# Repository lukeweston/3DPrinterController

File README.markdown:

3D printer / CNC machine controller:   

The final system will be broken across three boards, to allow for modularity, replacement of the modules individually, upgradability, and to allow enough space for proper
design of the power electronics.   

a) Microcontroller, UI, storage, display, connectivity etc.   
b) Power distribution, switching, heater control etc.   
c) Stepper motor drivers.   

Example image of 5-channel stepper motor controller board:

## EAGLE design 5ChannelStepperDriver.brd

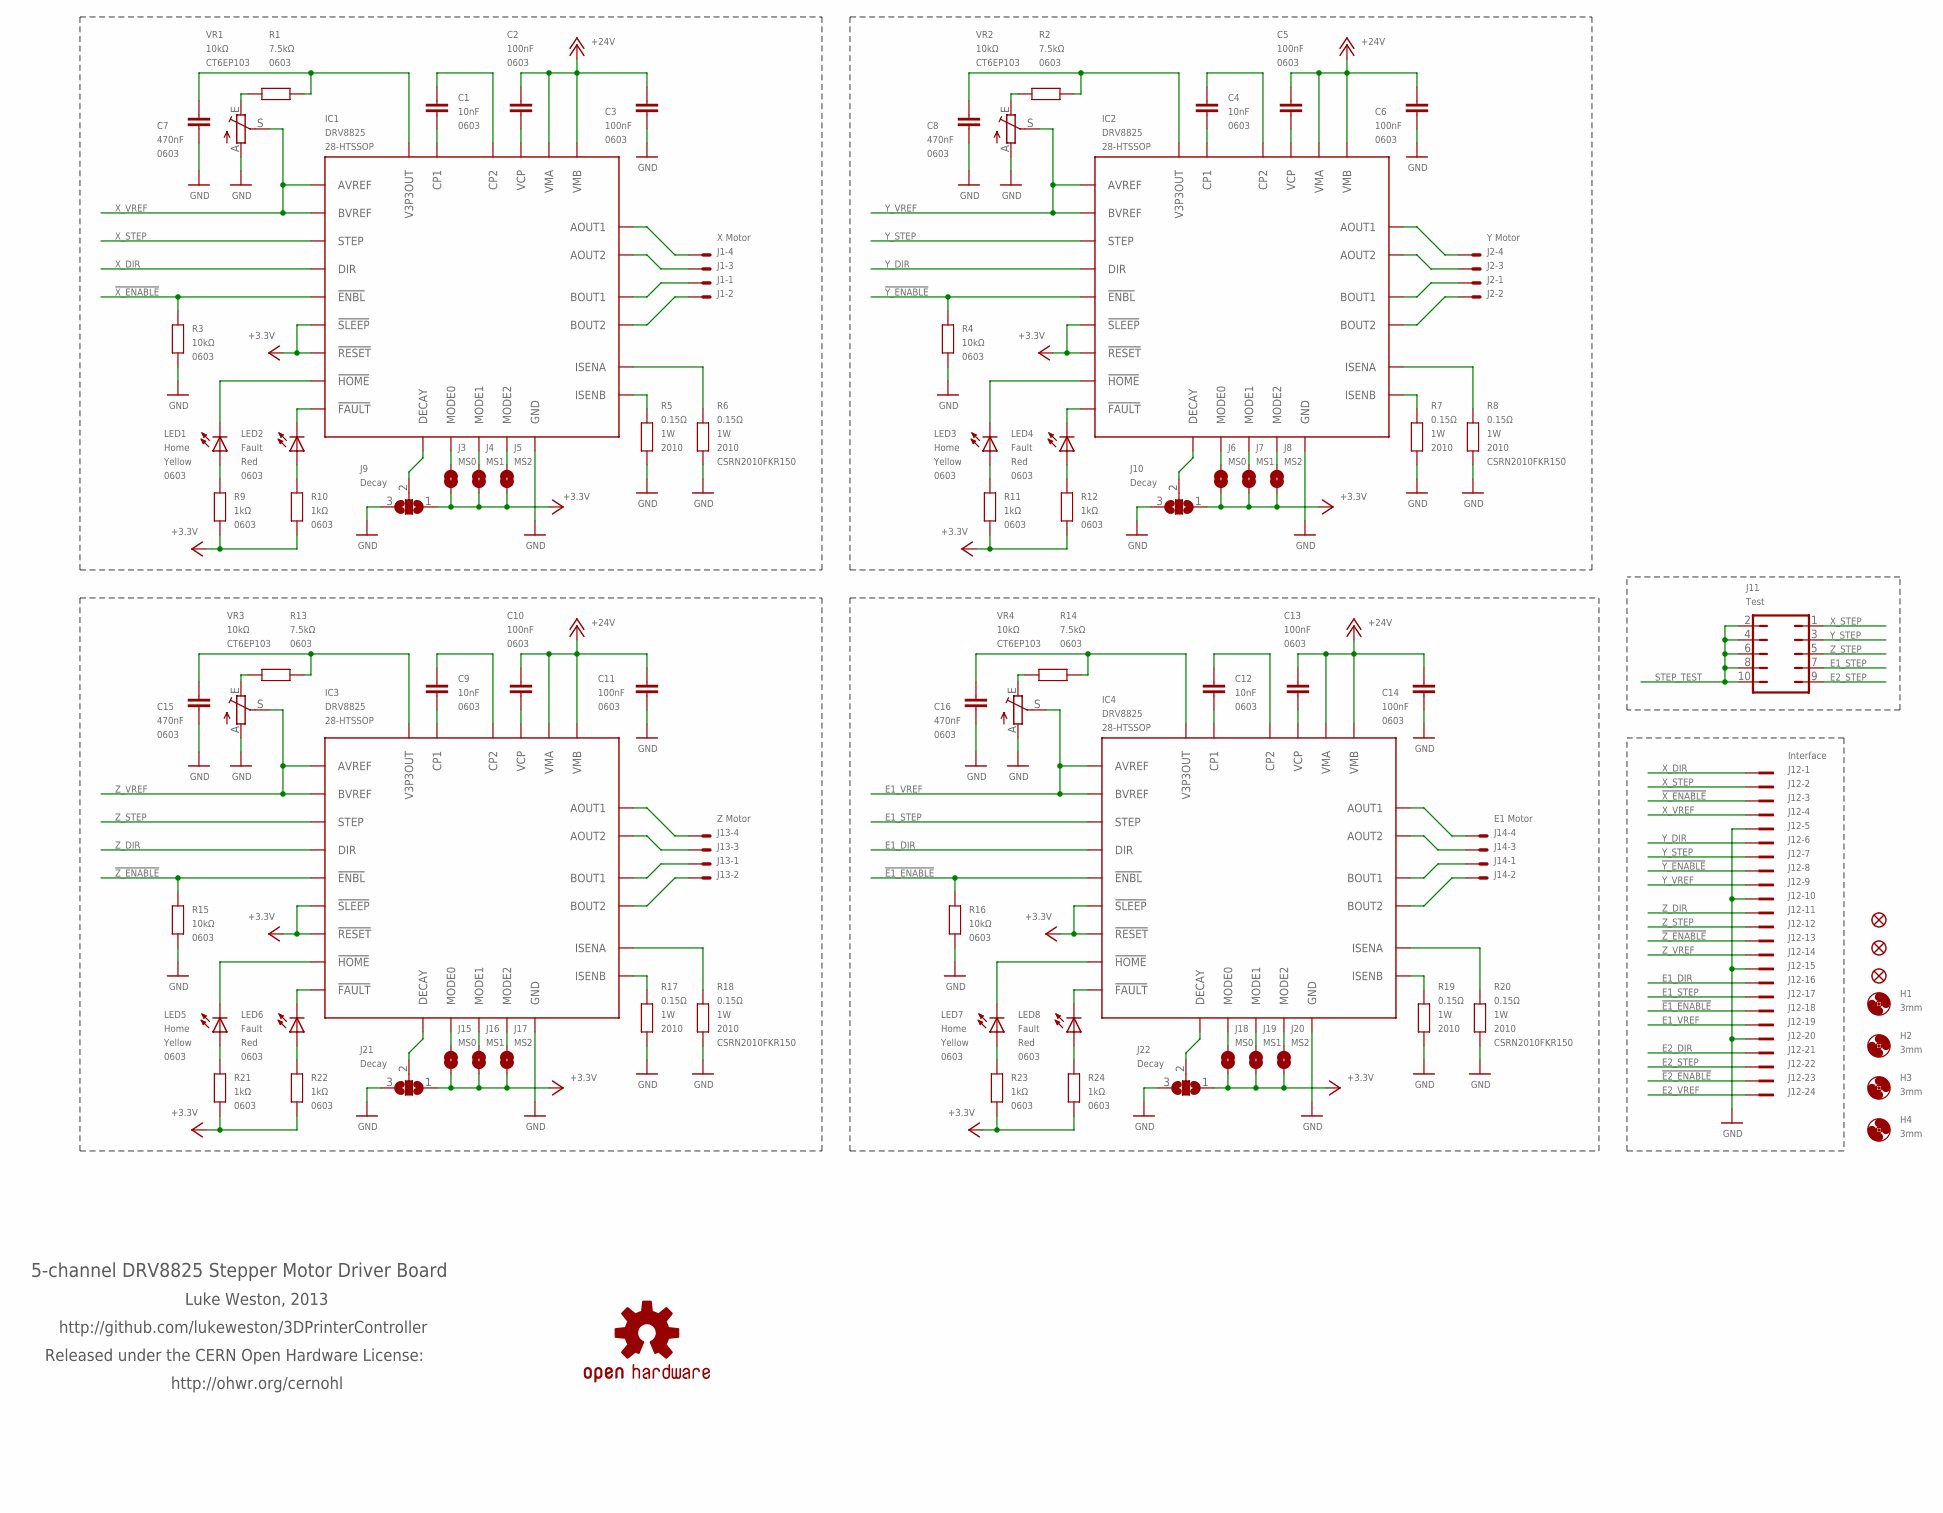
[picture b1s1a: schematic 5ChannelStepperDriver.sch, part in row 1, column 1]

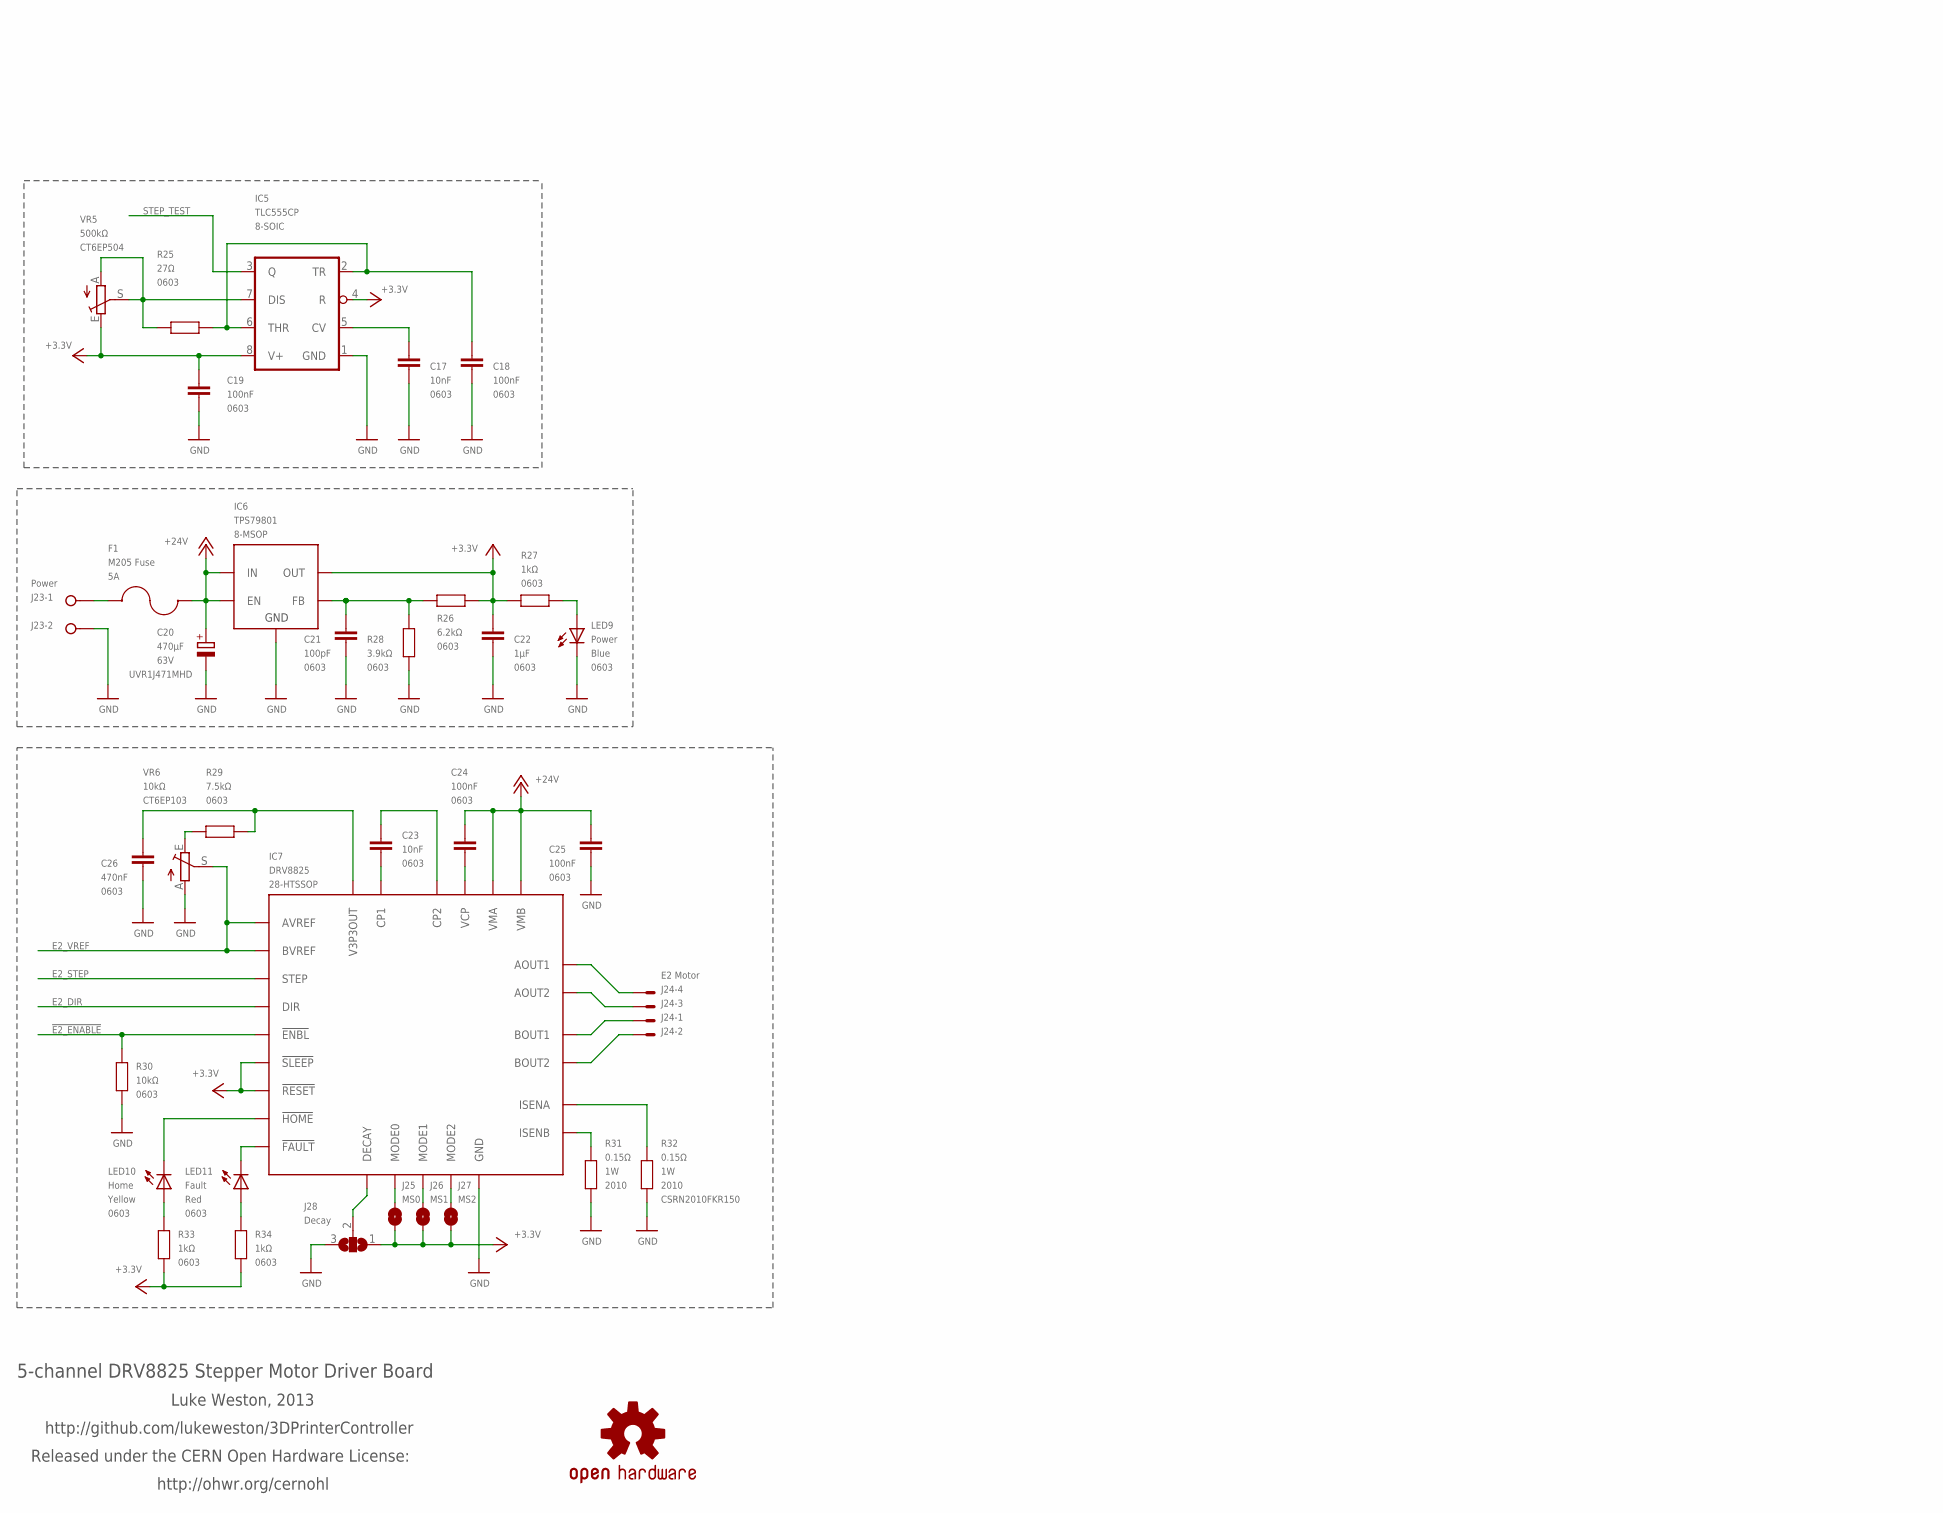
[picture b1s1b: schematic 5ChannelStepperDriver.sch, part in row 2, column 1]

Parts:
C1, C4, C9, C12, C17, C23: 10nF; 0603
C2, C3, C5, C6, C10, C11, C13, C14, C18, C19, C24, C25: 100nF; 0603
C7, C8, C15, C16, C26: 470nF; 0603
C20: 470µF; E5-13; VOLTAGE 63V
C21: 100pF; 0603
C22: 1µF; 0603
F1: M205 Fuse; FUSECLIP-FC211
H1, H2, H3, H4: 3mm; 3,0
IC1, IC2, IC3, IC4, IC7: DRV8825; R-PDSO-G28
IC5: TLC555CP; SO08
IC6: TPS79801; R-PDSO-G8
J1: X Motor; 7395-04
J2: Y Motor; 7395-04
J3, J6, J15, J18, J25: MS0; SJ
J4, J7, J16, J19, J26: MS1; SJ
J5, J8, J17, J20, J27: MS2; SJ
J9, J10, J21, J22, J28: Decay; SJ_2
J11: Test; JP5Q
J12: Interface; PAK100/2500-24
J13: Z Motor; 7395-04
J14: E1 Motor; 7395-04
J23: Power; W237-132
J24: E2 Motor; 7395-04
JP1, JP2, JP3: FIDUCIAL1X2; FIDUCIAL-1X2
LED1, LED3, LED5, LED7, LED10: Home; LED-0603
LED2, LED4, LED6, LED8, LED11: Fault; LED-0603
LED9: Power; LED-0603
R1, R2, R13, R14, R29: 7.5kΩ; 0603
R3, R4, R15, R16, R30: 10kΩ; 0603
R5, R6, R7, R8, R17, R18, R19, R20, R31, R32: 0.15Ω; R2010
R9, R10, R11, R12, R21, R22, R23, R24, R27, R33, R34: 1kΩ; 0603
R25: 27Ω; 0603
R26: 6.2kΩ; 0603
R28: 3.9kΩ; 0603
SY1, SY2: OSHW-LOGOS; OSHW-LOGO-S
VR1, VR2, VR3, VR4, VR6: 10kΩ; CT6
VR5: 500kΩ; CT6

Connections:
!E1_ENABLE: IC4.21 (!ENBL), J12.18, R16.1
!E2_ENABLE: IC7.21 (!ENBL), J12.23, R30.1
!X_ENABLE: IC1.21 (!ENBL), J12.3, R3.1
!Y_ENABLE: IC2.21 (!ENBL), J12.8, R4.1
!Z_ENABLE: IC3.21 (!ENBL), J12.13, R15.1
+3V3: C19.1, C22.1, IC1.16 (!RESET), IC1.17 (!SLEEP), IC2.16 (!RESET), IC2.17 (!SLEEP), IC3.16 (!RESET), IC3.17 (!SLEEP), IC4.16 (!RESET), IC4.17 (!SLEEP), IC5.4 (R), IC5.8 (V+), IC6.1 (OUT), IC7.16 (!RESET), IC7.17 (!SLEEP), J3.1, J4.1, J5.1, J6.1, J7.1, J8.1, J9.1, J10.1, J15.1, J16.1, J17.1, J18.1, J19.1, J20.1, J21.1, J22.1, J25.1, J26.1, J27.1, J28.1, R9.2, R10.2, R11.2, R12.2, R21.2, R22.2, R23.2, R24.2, R26.2, R27.2, R33.2, R34.2, VR5.E
+24V: C2.1, C3.1, C5.1, C6.1, C10.1, C11.1, C13.1, C14.1, C20.+, C24.1, C25.1, F1.3 (2), F1.4 (2), IC1.4 (VMA), IC1.11 (VMB), IC2.4 (VMA), IC2.11 (VMB), IC3.4 (VMA), IC3.11 (VMB), IC4.4 (VMA), IC4.11 (VMB), IC6.5 (EN), IC6.8 (IN), IC7.4 (VMA), IC7.11 (VMB)
E1_DIR: IC4.20 (DIR), J12.16
E1_STEP: IC4.22 (STEP), J11.7, J12.17
E1_VREF: IC4.12 (AVREF), IC4.13 (BVREF), J12.19, VR4.S
E2_DIR: IC7.20 (DIR), J12.21
E2_STEP: IC7.22 (STEP), J11.9, J12.22
E2_VREF: IC7.12 (AVREF), IC7.13 (BVREF), J12.24, VR6.S
GND: C3.2, C6.2, C7.2, C8.2, C11.2, C14.2, C15.2, C16.2, C17.2, C18.2, C19.2, C20.-, C21.2, C22.2, C25.2, C26.2, IC1.14 (GND), IC1.28 (GND), IC1.PAD (GND), IC2.14 (GND), IC2.28 (GND), IC2.PAD (GND), IC3.14 (GND), IC3.28 (GND), IC3.PAD (GND), IC4.14 (GND), IC4.28 (GND), IC4.PAD (GND), IC5.1 (GND), IC6.4 (GND), IC6.PAD (GND), IC7.14 (GND), IC7.28 (GND), IC7.PAD (GND), J9.3, J10.3, J12.5, J12.10, J12.15, J12.20, J21.3, J22.3, J23.2, J28.3, LED9.C, R3.2, R4.2, R5.2, R6.2, R7.2, R8.2, R15.2, R16.2, R17.2, R18.2, R19.2, R20.2, R28.2, R30.2, R31.2, R32.2, VR1.A, VR2.A, VR3.A, VR4.A, VR6.A
unnamed: IC1.5 (AOUT1), J1.4
unnamed: IC4.10 (BOUT1), J14.1
unnamed: IC3.10 (BOUT1), J13.1
unnamed: IC7.10 (BOUT1), J24.1
unnamed: IC7.7 (AOUT2), J24.3
unnamed: C7.1, IC1.15 (V3P3OUT), R1.1
unnamed: F1.1, F1.2 (1), J23.1
unnamed: R14.2, VR4.E
unnamed: C8.1, IC2.15 (V3P3OUT), R2.1
unnamed: C16.1, IC4.15 (V3P3OUT), R14.1
unnamed: C26.1, IC7.15 (V3P3OUT), R29.1
unnamed: R2.2, VR2.E
unnamed: R29.2, VR6.E
unnamed: R1.2, VR1.E
unnamed: C18.1, IC5.2 (TR), IC5.6 (THR), R25.1
unnamed: C15.1, IC3.15 (V3P3OUT), R13.1
unnamed: C21.1, IC6.2 (FB), R26.1, R28.1
unnamed: R13.2, VR3.E
unnamed: C17.1, IC5.5 (CV)
unnamed: LED9.A, R27.1
unnamed: IC5.7 (DIS), R25.2, VR5.A, VR5.S
unnamed: IC1.7 (AOUT2), J1.3
unnamed: IC1.10 (BOUT1), J1.1
unnamed: IC1.8 (BOUT2), J1.2
unnamed: C1.2, IC1.1 (CP1)
unnamed: C1.1, IC1.2 (CP2)
unnamed: IC1.19 (DECAY), J9.2
unnamed: C2.2, IC1.3 (VCP)
unnamed: IC1.6 (ISENA), R6.1
unnamed: IC3.5 (AOUT1), J13.4
unnamed: IC1.9 (ISENB), R5.1
unnamed: IC3.7 (AOUT2), J13.3
unnamed: IC3.8 (BOUT2), J13.2
unnamed: IC1.18 (!FAULT), LED2.C
unnamed: IC1.27 (!HOME), LED1.C
unnamed: LED1.A, R9.1
unnamed: LED2.A, R10.1
unnamed: IC1.25 (MODE1), J4.2
unnamed: IC1.26 (MODE2), J5.2
unnamed: IC1.24 (MODE0), J3.2
unnamed: C10.2, IC3.3 (VCP)
unnamed: IC3.6 (ISENA), R18.1
unnamed: IC3.9 (ISENB), R17.1
unnamed: IC3.18 (!FAULT), LED6.C
unnamed: IC3.27 (!HOME), LED5.C
unnamed: LED5.A, R21.1
unnamed: LED6.A, R22.1
unnamed: C9.2, IC3.1 (CP1)
unnamed: C9.1, IC3.2 (CP2)
unnamed: IC3.19 (DECAY), J21.2
unnamed: IC3.24 (MODE0), J15.2
unnamed: IC3.25 (MODE1), J16.2
unnamed: IC3.26 (MODE2), J17.2
unnamed: IC2.5 (AOUT1), J2.4
unnamed: IC2.7 (AOUT2), J2.3
unnamed: IC2.10 (BOUT1), J2.1
unnamed: IC2.8 (BOUT2), J2.2
unnamed: C5.2, IC2.3 (VCP)
unnamed: IC2.6 (ISENA), R8.1
unnamed: IC2.9 (ISENB), R7.1
unnamed: IC2.18 (!FAULT), LED4.C
unnamed: IC2.27 (!HOME), LED3.C
unnamed: LED3.A, R11.1
unnamed: LED4.A, R12.1
unnamed: C4.2, IC2.1 (CP1)
unnamed: C4.1, IC2.2 (CP2)
unnamed: IC2.19 (DECAY), J10.2
unnamed: IC2.24 (MODE0), J6.2
unnamed: IC2.25 (MODE1), J7.2
unnamed: IC2.26 (MODE2), J8.2
unnamed: IC4.5 (AOUT1), J14.4
unnamed: IC4.7 (AOUT2), J14.3
unnamed: IC4.8 (BOUT2), J14.2
unnamed: C13.2, IC4.3 (VCP)
unnamed: IC4.6 (ISENA), R20.1
unnamed: IC4.9 (ISENB), R19.1
unnamed: IC4.18 (!FAULT), LED8.C
unnamed: IC4.27 (!HOME), LED7.C
unnamed: LED7.A, R23.1
unnamed: LED8.A, R24.1
unnamed: C12.2, IC4.1 (CP1)
unnamed: C12.1, IC4.2 (CP2)
unnamed: IC4.19 (DECAY), J22.2
unnamed: IC4.24 (MODE0), J18.2
unnamed: IC4.25 (MODE1), J19.2
unnamed: IC4.26 (MODE2), J20.2
unnamed: IC7.5 (AOUT1), J24.4
unnamed: IC7.8 (BOUT2), J24.2
unnamed: C24.2, IC7.3 (VCP)
unnamed: IC7.6 (ISENA), R32.1
unnamed: IC7.9 (ISENB), R31.1
unnamed: IC7.18 (!FAULT), LED11.C
unnamed: IC7.27 (!HOME), LED10.C
unnamed: LED10.A, R33.1
unnamed: LED11.A, R34.1
unnamed: C23.2, IC7.1 (CP1)
unnamed: C23.1, IC7.2 (CP2)
unnamed: IC7.19 (DECAY), J28.2
unnamed: IC7.24 (MODE0), J25.2
unnamed: IC7.25 (MODE1), J26.2
unnamed: IC7.26 (MODE2), J27.2
STEP_TEST: IC5.3 (Q), J11.2, J11.4, J11.6, J11.8, J11.10
X_DIR: IC1.20 (DIR), J12.1
X_STEP: IC1.22 (STEP), J11.1, J12.2
X_VREF: IC1.12 (AVREF), IC1.13 (BVREF), J12.4, VR1.S
Y_DIR: IC2.20 (DIR), J12.6
Y_STEP: IC2.22 (STEP), J11.3, J12.7
Y_VREF: IC2.12 (AVREF), IC2.13 (BVREF), J12.9, VR2.S
Z_DIR: IC3.20 (DIR), J12.11
Z_STEP: IC3.22 (STEP), J11.5, J12.12
Z_VREF: IC3.12 (AVREF), IC3.13 (BVREF), J12.14, VR3.S

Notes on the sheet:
5-channel DRV8825 Stepper Motor Driver Board
Luke Weston, 2013
http://github.com/lukeweston/3DPrinterController
Released under the CERN Open Hardware License:
http://ohwr.org/cernohl

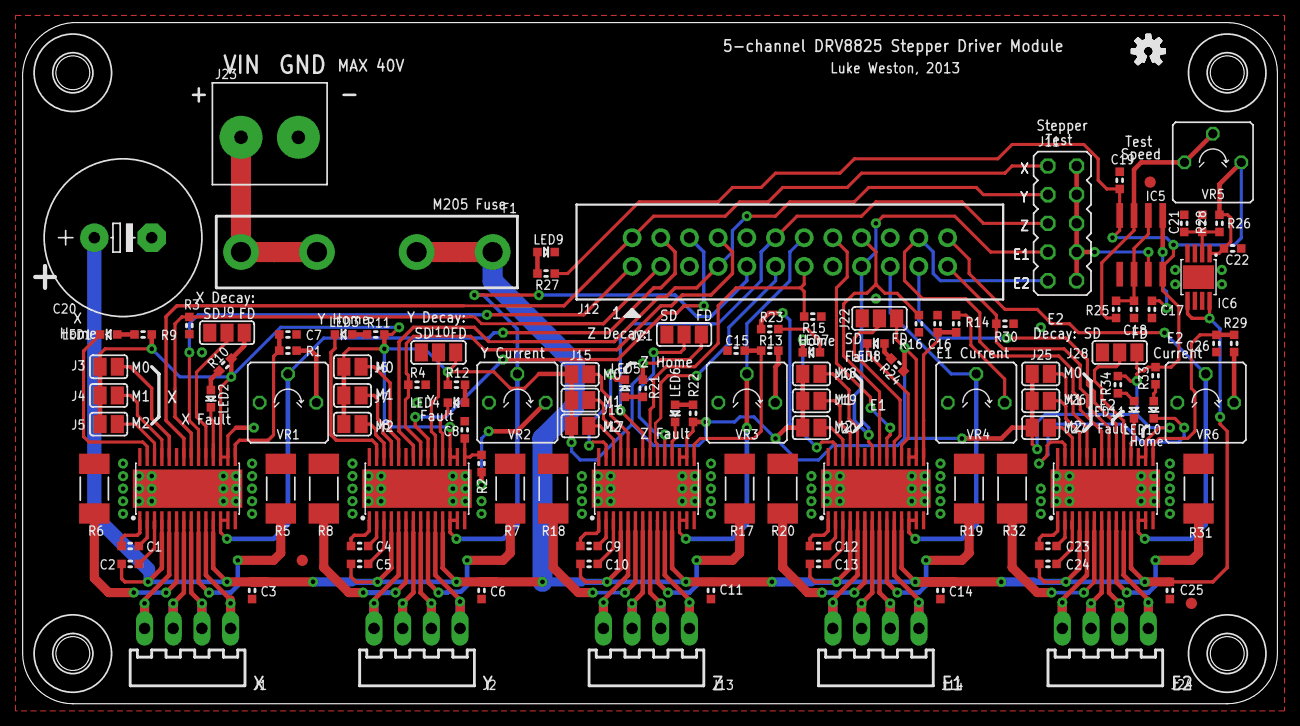
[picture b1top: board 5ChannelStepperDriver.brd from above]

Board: 2 copper layers, 111.1 x 60.3 mm, 122 parts (0 on the bottom side), 125 nets.

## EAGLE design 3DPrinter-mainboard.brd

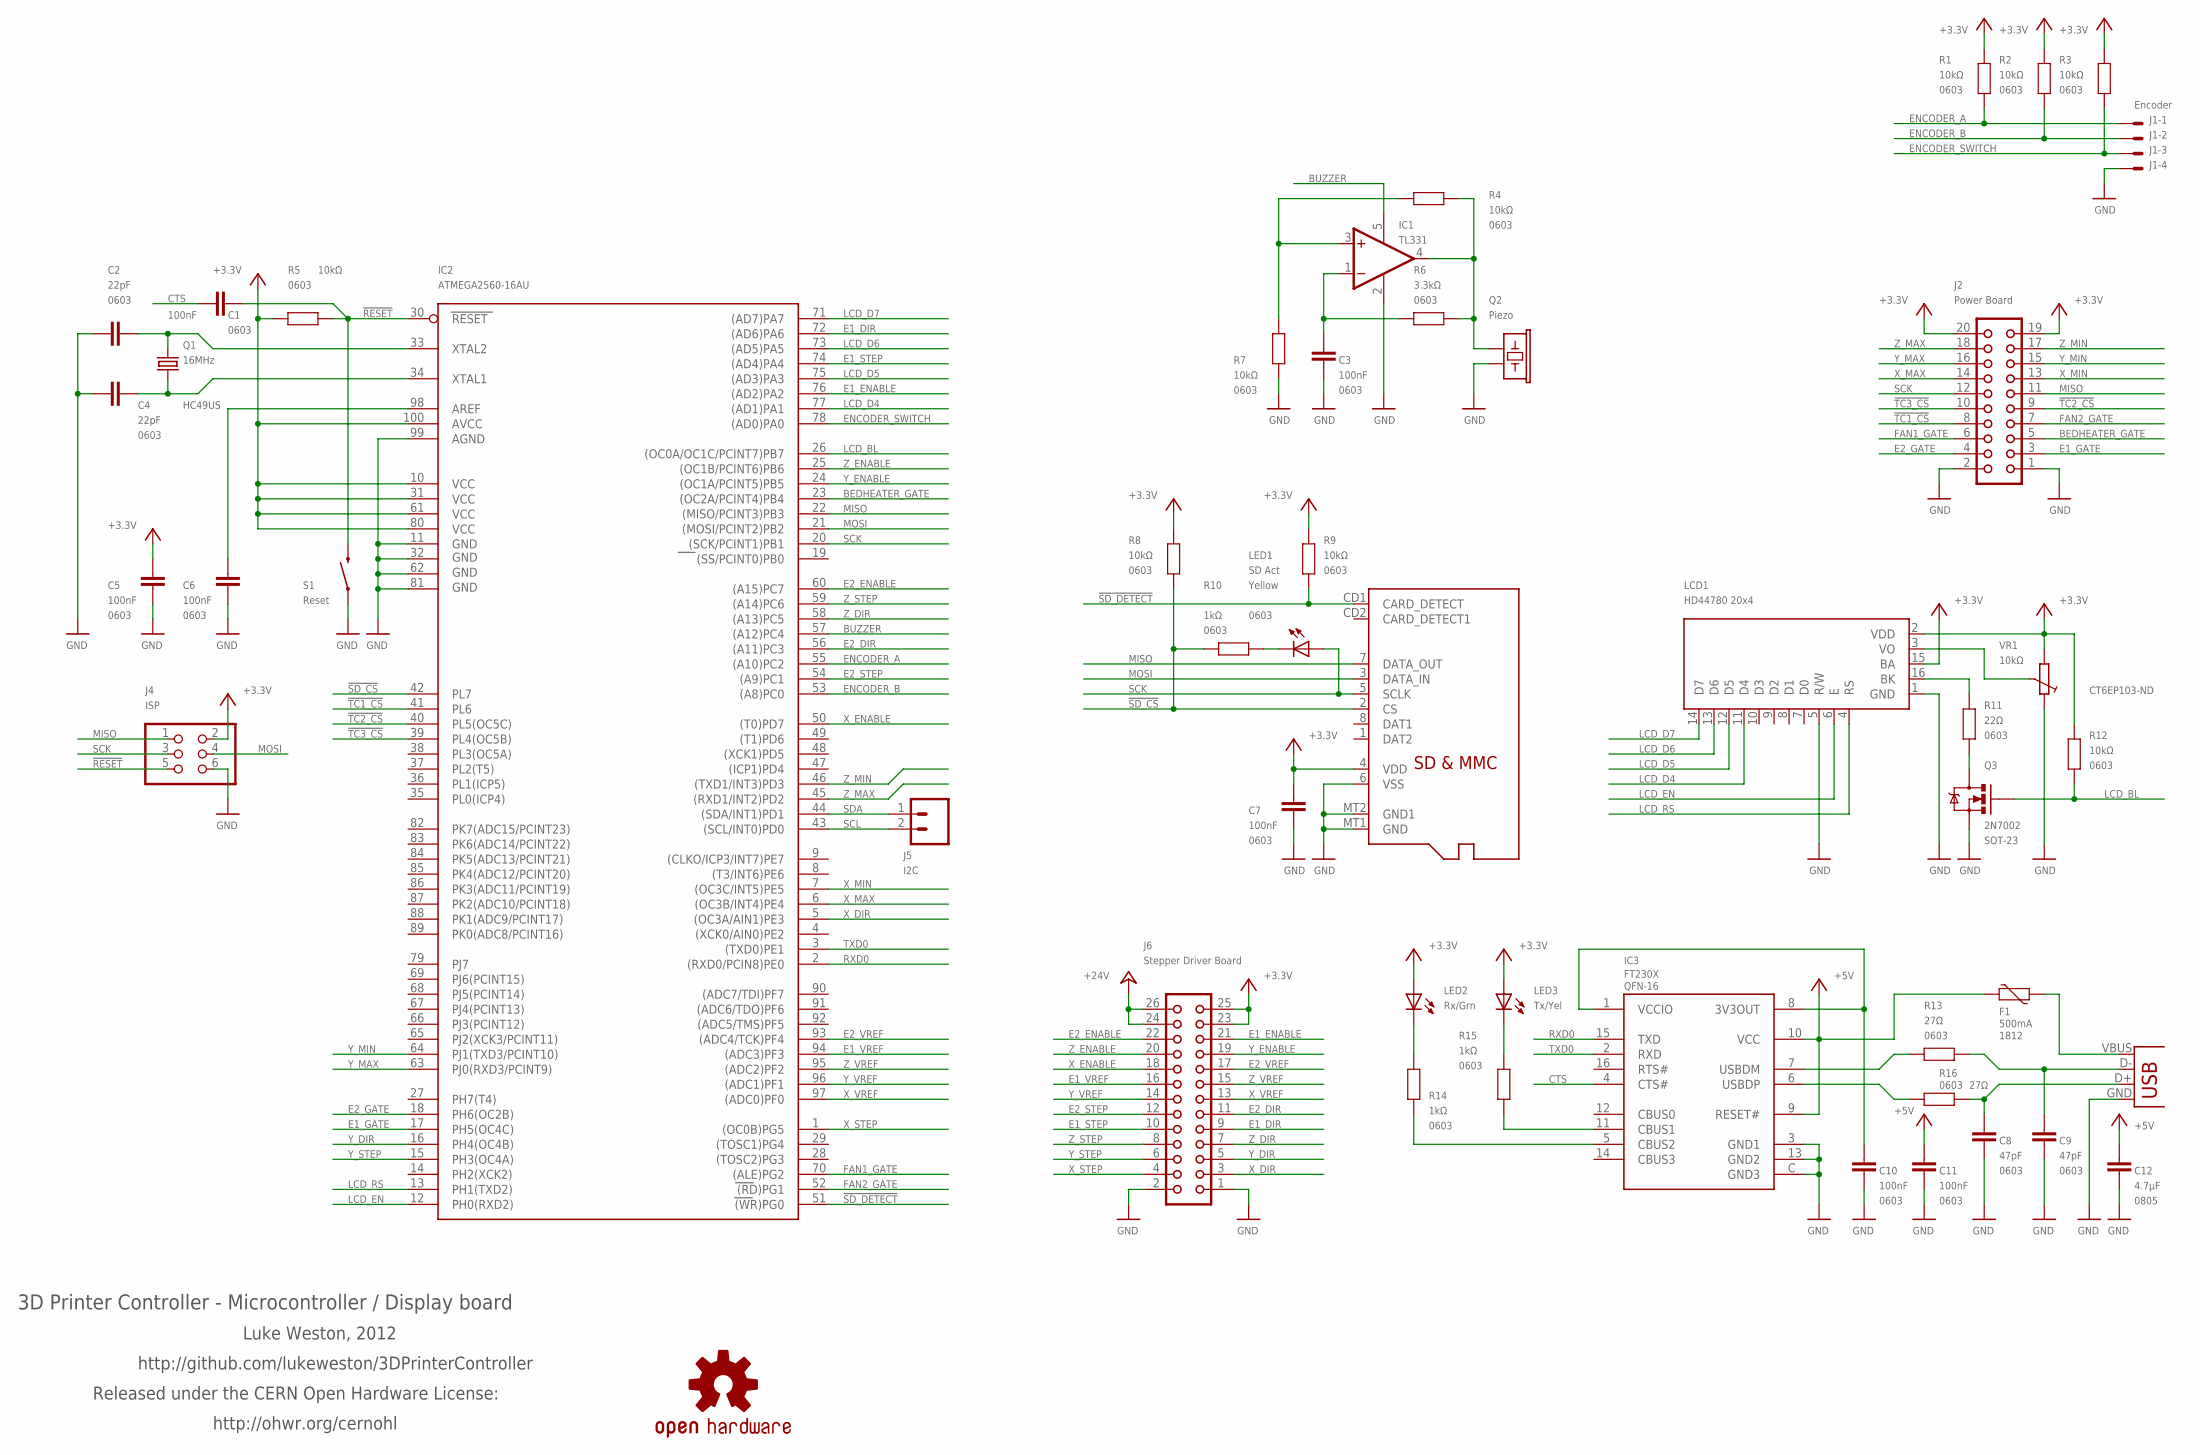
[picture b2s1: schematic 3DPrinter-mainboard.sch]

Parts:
C1, C3, C5, C6, C7, C10, C11: 100nF; 0603
C2, C4: 22pF; 0603
C8, C9: 47pF; 0603
C12: 4.7µF; 0805
F1: 500mA; 1812
IC1: TL331; DBV-R-PDSO-G5
IC2: ATMEGA2560-16AU; TQFP100
IC3: FT230X; QFN4X4-16
J1: Encoder; 7395-04
J2: Power Board; CON20L
J3: MicroSD Card; ADAFRUIT_MICROSD
J4: ISP; 2X03
J5: I2C; 1X02
J6: Stepper Driver Board; CON26L
LCD1: HD44780 20x4; HDM20416L
LED1: SD Act; LED-0603
LED2: Rx/Grn; LED-0603
LED3: Tx/Yel; LED-0603
Q1: 16MHz; HC49US
Q2: Piezo; FREETRONICS-MASTER-V1_BUZZER-12X12-SMT
Q3: 2N7002; SOT23-3
R1, R2, R3, R4, R5, R7, R8, R9, R12: 10kΩ; 0603
R6: 3.3kΩ; 0603
R10, R14, R15: 1kΩ; 0603
R11: 22Ω; 0603
R13, R16: 27Ω; 0603
S1: Reset; TACTILE_SWITCH_SMD
SY: OSHW-LOGOS; OSHW-LOGO-S
VR1: 10kΩ; CT6
X1: USB-MICROB

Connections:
!RESET: C1.2, IC2.30 (RESET), J4.5, R5.2, S1.3 (2)
!SD_CS: IC2.42 (PL7), J3.2 (CS), R8.2, R10.2
!SD_DETECT: IC2.51 ((WR)PG0), J3.CD1 (CARD_DETECT), R9.2
!TC1_CS: IC2.41 (PL6), J2.8
!TC2_CS: IC2.40 (PL5(OC5C)), J2.9
!TC3_CS: IC2.39 (PL4(OC5B)), J2.10
+3V3: C5.1, C7.1, IC2.10 (VCC), IC2.31 (VCC1), IC2.61 (VCC2), IC2.80 (VCC3), IC2.100 (AVCC), J2.19, J2.20, J3.4 (VDD), J4.2, J6.23, J6.25, LCD1.2 (VDD), LCD1.15 (BA), LED2.A, LED3.A, R1.1, R2.1, R3.1, R5.1, R8.1, R9.1, R12.1, VR1.A
+5V: C11.1, C12.1, F1.2, IC3.9 (RESET#), IC3.10 (VCC)
+24V: J6.24, J6.26
BEDHEATER_GATE: IC2.23 ((OC2A/PCINT4)PB4), J2.5
BUZZER: IC1.5 (V+), IC2.57 ((A12)PC4)
CTS: C1.1, IC3.4 (CTS#)
E1_DIR: IC2.72 ((AD6)PA6), J6.9
E1_ENABLE: IC2.76 ((AD2)PA2), J6.21
E1_GATE: IC2.17 (PH5(OC4C)), J2.3
E1_STEP: IC2.74 ((AD4)PA4), J6.10
E1_VREF: IC2.94 ((ADC3)PF3), J6.16
E2_DIR: IC2.56 ((A11)PC3), J6.11
E2_ENABLE: IC2.60 ((A15)PC7), J6.22
E2_GATE: IC2.18 (PH6(OC2B)), J2.4
E2_STEP: IC2.54 ((A9)PC1), J6.12
E2_VREF: IC2.93 ((ADC4/TCK)PF4), J6.17
ENCODER_A: IC2.55 ((A10)PC2), J1.1, R1.2
ENCODER_B: IC2.53 ((A8)PC0), J1.2, R2.2
ENCODER_SWITCH: IC2.78 ((AD0)PA0), J1.3, R3.2
FAN1_GATE: IC2.70 ((ALE)PG2), J2.6
FAN2_GATE: IC2.52 ((RD)PG1), J2.7
GND: C2.1, C3.2, C4.1, C5.2, C6.2, C7.2, C8.2, C9.2, C10.2, C11.2, C12.2, IC1.2 (GND), IC2.11 (GND), IC2.32 (GND1), IC2.62 (GND2), IC2.81 (GND3), IC2.99 (AGND), IC3.3 (GND1), IC3.13 (GND2), IC3.C (GND3), J1.4, J2.1, J2.2, J3.6 (VSS), J3.MT1 (GND), J3.MT2 (GND1), J4.6, J6.1, J6.2, LCD1.1 (GND), LCD1.5 (R/W), Q2.1, Q3.2 (S), R7.1, S1.1, VR1.E, X1.GND
LCD_BL: IC2.26 ((OC0A/OC1C/PCINT7)PB7), Q3.1 (G), R12.2
LCD_D4: IC2.77 ((AD1)PA1), LCD1.11 (D4)
LCD_D5: IC2.75 ((AD3)PA3), LCD1.12 (D5)
LCD_D6: IC2.73 ((AD5)PA5), LCD1.13 (D6)
LCD_D7: IC2.71 ((AD7)PA7), LCD1.14 (D7)
LCD_EN: IC2.12 (PH0(RXD2)), LCD1.6 (E)
LCD_RS: IC2.13 (PH1(TXD2)), LCD1.4 (RS)
MISO: IC2.22 ((MISO/PCINT3)PB3), J2.11, J3.7 (DATA_OUT), J4.1
MOSI: IC2.21 ((MOSI/PCINT2)PB2), J3.3 (DATA_IN), J4.4
unnamed: LCD1.16 (BK), R11.1
unnamed: LED3.C, R15.1
unnamed: Q3.3 (D), R11.2
unnamed: IC3.7 (USBDM), R13.1
unnamed: C2.2, IC2.33 (XTAL2), Q1.2
unnamed: IC3.11 (CBUS1), R15.2
unnamed: LED2.C, R14.1
unnamed: IC3.5 (CBUS2), R14.2
unnamed: LED1.C, R10.1
unnamed: C3.1, IC1.1 (-IN), R6.2
unnamed: IC1.3 (+IN), R4.2, R7.2
unnamed: IC1.4 (OUT), Q2.2, R4.1, R6.1
unnamed: C4.2, IC2.34 (XTAL1), Q1.1
unnamed: C10.1, IC3.1 (VCCIO), IC3.8 (3V3OUT)
unnamed: C6.1, IC2.98 (AREF)
unnamed: IC3.6 (USBDP), R16.1
unnamed: C8.1, R16.2, X1.D+
unnamed: C9.1, R13.2, X1.D-
unnamed: F1.1, X1.VBUS
unnamed: LCD1.3 (VO), VR1.S
RXD0: IC2.2 ((RXD0/PCIN8)PE0), IC3.15 (TXD)
SCK: IC2.20 ((SCK/PCINT1)PB1), J2.12, J3.5 (SCLK), J4.3, LED1.A
SCL: IC2.43 ((SCL/INT0)PD0), J5.2
SDA: IC2.44 ((SDA/INT1)PD1), J5.1
TXD0: IC2.3 ((TXD0)PE1), IC3.2 (RXD)
X_DIR: IC2.5 ((OC3A/AIN1)PE3), J6.3
X_ENABLE: IC2.50 ((T0)PD7), J6.18
X_MAX: IC2.6 ((OC3B/INT4)PE4), J2.14
X_MIN: IC2.7 ((OC3C/INT5)PE5), J2.13
X_STEP: IC2.1 ((OC0B)PG5), J6.4
X_VREF: IC2.97 ((ADC0)PF0), J6.13
Y_DIR: IC2.16 (PH4(OC4B)), J6.5
Y_ENABLE: IC2.24 ((OC1A/PCINT5)PB5), J6.19
Y_MAX: IC2.63 (PJ0(RXD3/PCINT9)), J2.16
Y_MIN: IC2.64 (PJ1(TXD3/PCINT10)), J2.15
Y_STEP: IC2.15 (PH3(OC4A)), J6.6
Y_VREF: IC2.96 ((ADC1)PF1), J6.14
Z_DIR: IC2.58 ((A13)PC5), J6.7
Z_ENABLE: IC2.25 ((OC1B/PCINT6)PB6), J6.20
Z_MAX: IC2.45 ((RXD1/INT2)PD2), J2.18
Z_MIN: IC2.46 ((TXD1/INT3)PD3), J2.17
Z_STEP: IC2.59 ((A14)PC6), J6.8
Z_VREF: IC2.95 ((ADC2)PF2), J6.15

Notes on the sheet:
3D Printer Controller - Microcontroller / Display board
Luke Weston, 2012
http://github.com/lukeweston/3DPrinterController
Released under the CERN Open Hardware License:
http://ohwr.org/cernohl
FT230X

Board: 2 copper layers, 49 parts (0 on the bottom side), 80 nets, no tracks yet.

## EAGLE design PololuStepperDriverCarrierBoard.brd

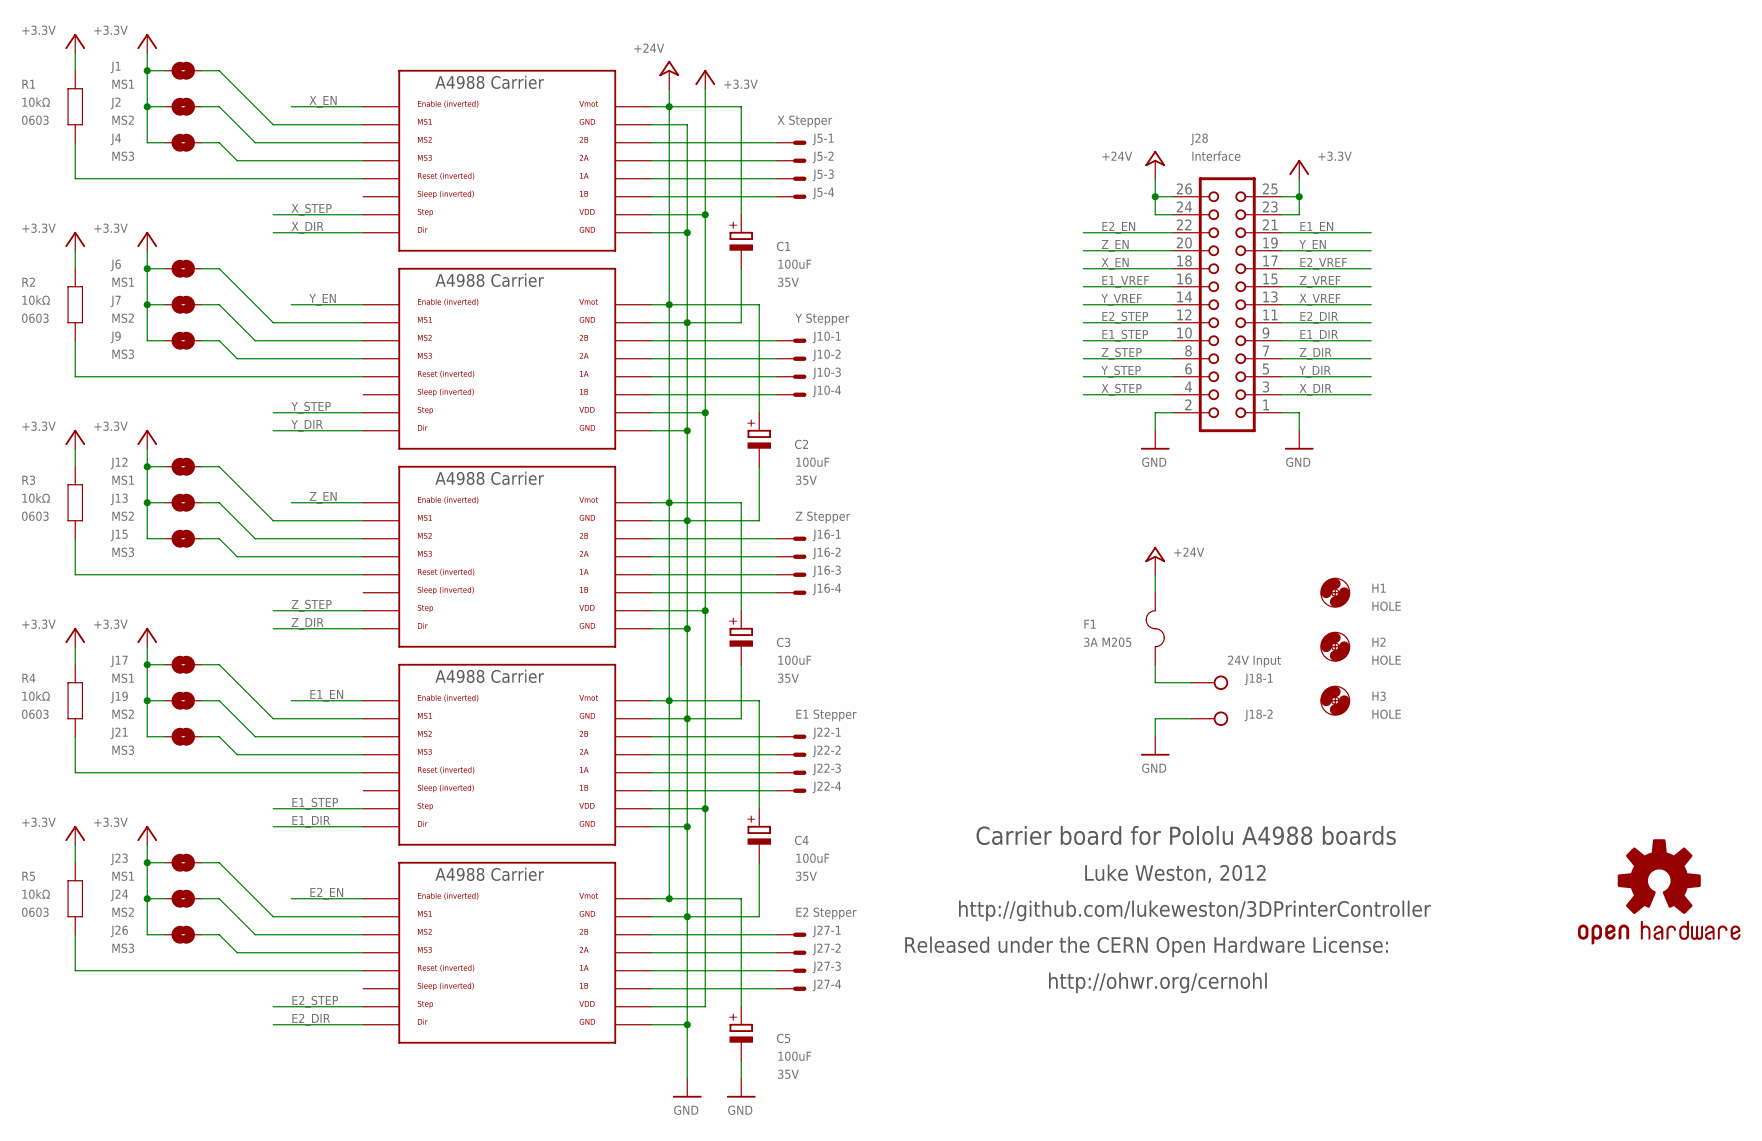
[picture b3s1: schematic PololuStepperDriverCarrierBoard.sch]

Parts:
C1, C2, C3, C4, C5: 100uF; E2,5-6; VOLTAGE 35V
F1: 3A M205; SHK20L
H1, H2, H3: HOLE; 3,2
J1, J6, J12, J17, J23: MS1; SJ
J2, J7, J13, J19, J24: MS2; SJ
J3, J8, J14, J20, J25: A4988BREAKOUT
J4, J9, J15, J21, J26: MS3; SJ
J5: X Stepper; 7395-04
J10: Y Stepper; 7395-04
J16: Z Stepper; 7395-04
J18: 24V Input; W237-132
J22: E1 Stepper; 7395-04
J27: E2 Stepper; 7395-04
J28: Interface; CON26L
R1, R2, R3, R4, R5: 10kΩ; 0603
SY1: OSHW-LOGOS; OSHW-LOGO-S

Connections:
+3V3: J1.1, J2.1, J3.VDD, J4.1, J6.1, J7.1, J8.VDD, J9.1, J12.1, J13.1, J14.VDD, J15.1, J17.1, J19.1, J20.VDD, J21.1, J23.1, J24.1, J25.VDD, J26.1, J28.23, J28.25, R1.1, R2.1, R3.1, R4.1, R5.1
+24V: C1.+, C2.+, C3.+, C4.+, C5.+, F1.2A (2), J3.VMOT, J8.VMOT, J14.VMOT, J20.VMOT, J25.VMOT, J28.24, J28.26
E1_DIR: J20.DIR, J28.9
E1_EN: J20.EN, J28.21
E1_STEP: J20.STEP, J28.10
E1_VREF: J28.16
E2_DIR: J25.DIR, J28.11
E2_EN: J25.EN, J28.22
E2_STEP: J25.STEP, J28.12
E2_VREF: J28.17
GND: C1.-, C2.-, C3.-, C4.-, C5.-, J3.GND, J3.GND@0 (GND), J8.GND, J8.GND@0 (GND), J14.GND, J14.GND@0 (GND), J18.2, J20.GND, J20.GND@0 (GND), J25.GND, J25.GND@0 (GND), J28.1, J28.2
unnamed: J8.RST, R2.2
unnamed: J3.2B, J5.1
unnamed: J3.1B, J5.4
unnamed: J3.1A, J5.3
unnamed: J3.2A, J5.2
unnamed: J8.2B, J10.1
unnamed: J8.1A, J10.3
unnamed: J8.2A, J10.2
unnamed: J8.1B, J10.4
unnamed: J14.2B, J16.1
unnamed: J14.1B, J16.4
unnamed: J14.1A, J16.3
unnamed: J14.2A, J16.2
unnamed: J20.2A, J22.2
unnamed: J20.2B, J22.1
unnamed: J20.1A, J22.3
unnamed: J20.1B, J22.4
unnamed: J25.2B, J27.1
unnamed: J25.2A, J27.2
unnamed: J25.1A, J27.3
unnamed: J25.1B, J27.4
unnamed: J3.RST, R1.2
unnamed: J8.MS3, J9.2
unnamed: J7.2, J8.MS2
unnamed: J3.MS3, J4.2
unnamed: J2.2, J3.MS2
unnamed: J1.2, J3.MS1
unnamed: J6.2, J8.MS1
unnamed: J14.RST, R3.2
unnamed: J14.MS3, J15.2
unnamed: J13.2, J14.MS2
unnamed: J12.2, J14.MS1
unnamed: J25.RST, R5.2
unnamed: J25.MS3, J26.2
unnamed: J24.2, J25.MS2
unnamed: J23.2, J25.MS1
unnamed: J20.RST, R4.2
unnamed: J20.MS3, J21.2
unnamed: J19.2, J20.MS2
unnamed: J17.2, J20.MS1
unnamed: F1.1A (1), J18.1
X_DIR: J3.DIR, J28.3
X_EN: J3.EN, J28.18
X_STEP: J3.STEP, J28.4
X_VREF: J28.13
Y_DIR: J8.DIR, J28.5
Y_EN: J8.EN, J28.19
Y_STEP: J8.STEP, J28.6
Y_VREF: J28.14
Z_DIR: J14.DIR, J28.7
Z_EN: J14.EN, J28.20
Z_STEP: J14.STEP, J28.8
Z_VREF: J28.15

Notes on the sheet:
Carrier board for Pololu A4988 boards
Luke Weston, 2012
http://github.com/lukeweston/3DPrinterController
Released under the CERN Open Hardware License:
http://ohwr.org/cernohl

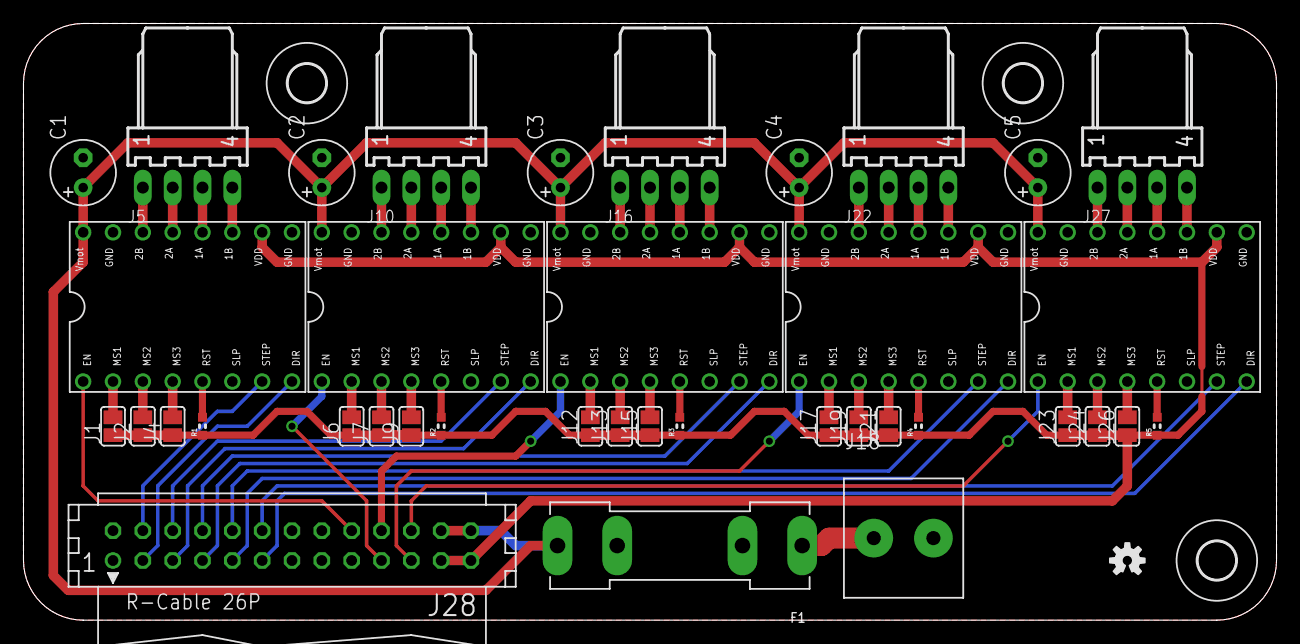
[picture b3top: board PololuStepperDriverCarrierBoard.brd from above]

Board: 2 copper layers, 106.7 x 50.8 mm, 42 parts (0 on the bottom side), 59 nets.
